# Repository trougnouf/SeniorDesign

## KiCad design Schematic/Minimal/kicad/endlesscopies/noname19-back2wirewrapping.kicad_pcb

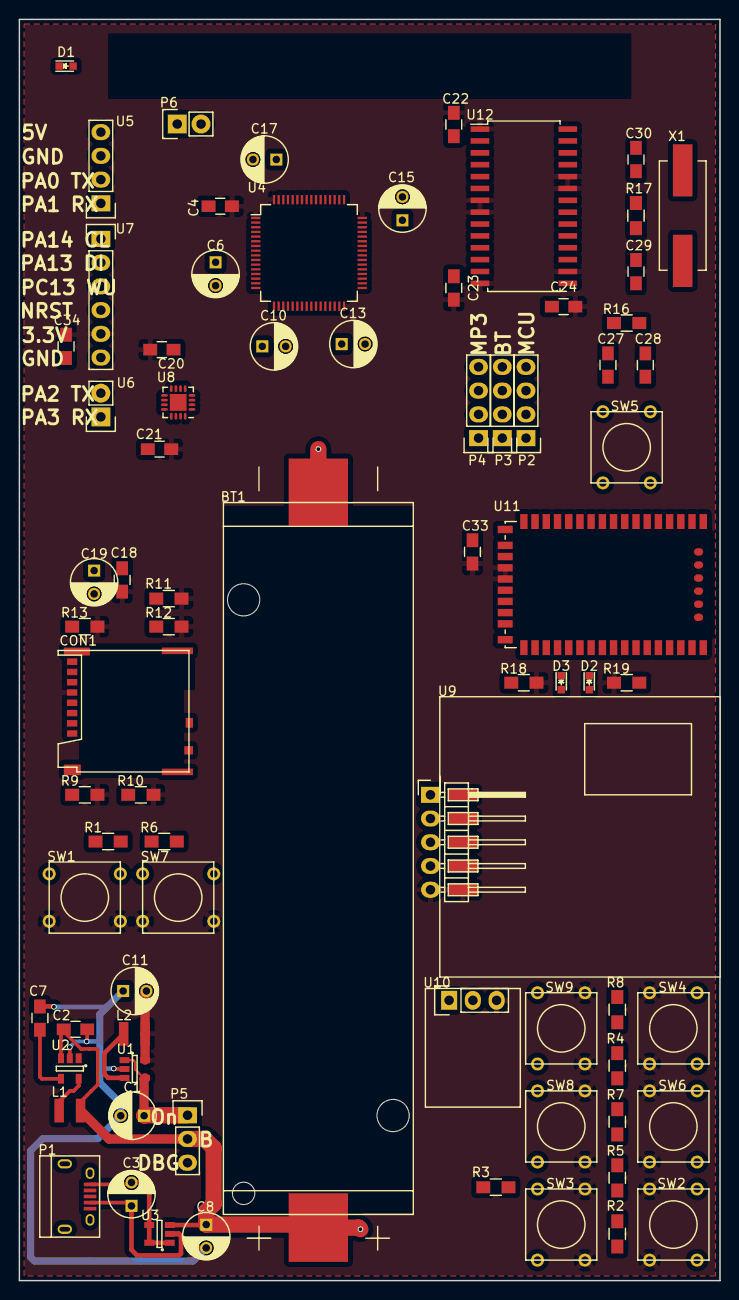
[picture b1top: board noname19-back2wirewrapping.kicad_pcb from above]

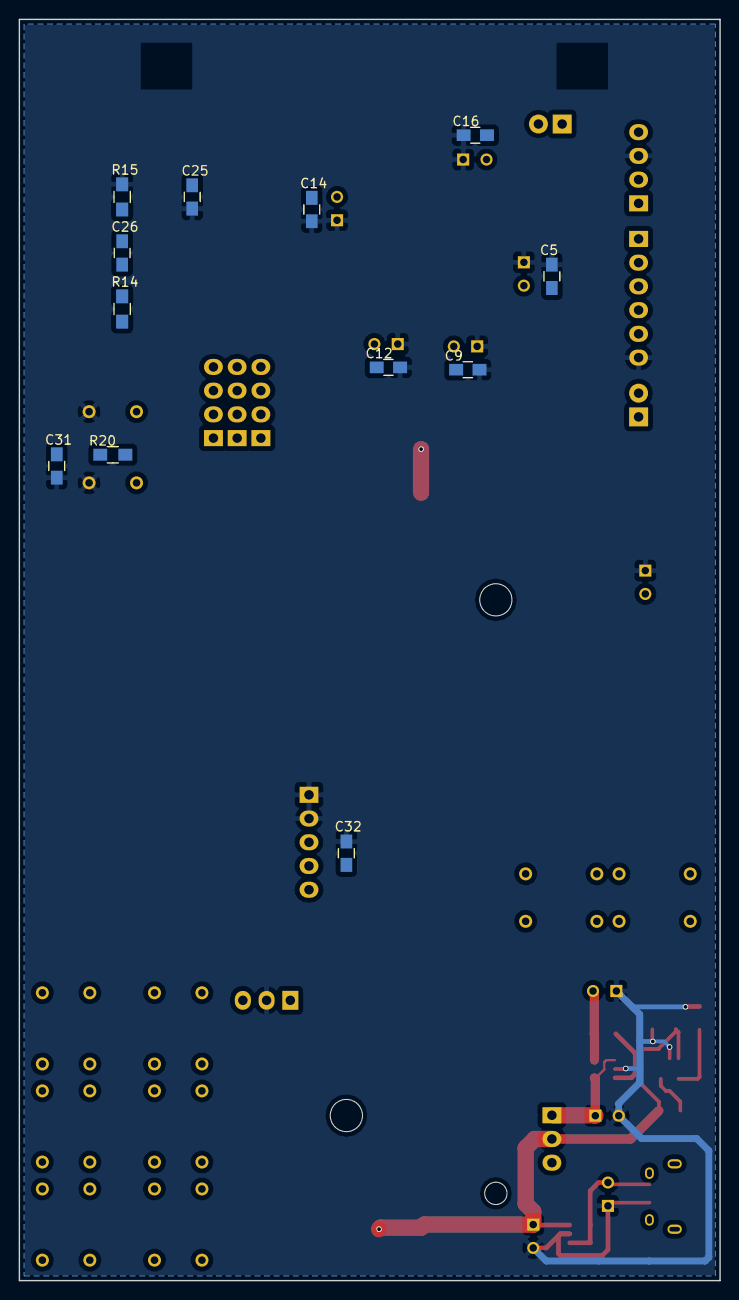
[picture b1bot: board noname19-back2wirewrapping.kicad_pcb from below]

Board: 2 copper layers, 75.0 x 135.0 mm, 89 parts (12 on the bottom side), 76 nets.

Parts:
BT1: Battery; 18650BatteryHolder
C1, C11: 10uF; C_Radial_D5_L11_P2.5
C2: 4.7uF; C_0805_HandSoldering
C3, C8: 1uF; C_Radial_D5_L11_P2.5
C4, C5, C9, C12, C14, C16, C19, C20, C21, C22, C23, C24, C25, C26, C31, C32, C33, C34: 0.1uF; C_0805_HandSoldering
C6, C10, C13, C15, C17: 4.7uF; C_Radial_D5_L11_P2.5
C7: 10uF; C_0805_HandSoldering
C18: 47uF; C_Radial_D5_L11_P2.5
C27: 470pF; C_0805_HandSoldering
C28: 4.7nF; C_0805_HandSoldering
C29, C30: 22pF; C_0805_HandSoldering
CON1: uSD_Card; MicroSD
D1: Led_Small; LED_0603
D2: Led_B; LED_0603
D3: Led_R; LED_0603
L1, L2: 4.7uH; Neosid_Inductor_SM-NE29_SMD1008
P1: USB_B; USB_Micro-B
P2, P3, P4: CONN_01X04; Pin_Header_Straight_1x04
P5: CONN_01X03; Pin_Header_Straight_1x03
P6: CONN_01X02; Socket_Strip_Straight_1x02
R1, R2, R3, R4, R5, R6, R7, R8, R20: 10K; R_0805_HandSoldering
R9, R10, R11, R12, R13: 47K; R_0805_HandSoldering
R14, R15: 4.7; R_0805_HandSoldering
R16: 1k; R_0805_HandSoldering
R17: 1M; R_0805_HandSoldering
R18: 470; R_0805_HandSoldering
R19: 47; R_0805_HandSoldering
SW1, SW2, SW3, SW4, SW5, SW6, SW7, SW8, SW9: SW_PUSH; SW_PUSH_SMALL
U1: PAM2301; SOT-23-5
U2: XC9140; SOT-23-5
U3: MCP73811/2; SOT-23-5
U4: STM32L476R; LQFP-64_10x10mm_Pitch0.5mm
U5: Lightware_SF10/A; Socket_Strip_Straight_1x04_3467
U6: UART; Socket_Strip_Straight_1x02
U7: DebugPins; Socket_Strip_Straight_1x06
U8: MLX90393; QFN-16-1EP_3x3mm_Pitch0.5mm
U9: LS20031; LS20031+H
U10: ADMP401-BB; INMP401-bb
U11: RN-52
U12: STA013; SOIC-28_7.5x17.9mm_Pitch1.27mm
X1: 14.7456MHz; Crystal_HC49-SD_SMD

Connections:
+3V3: C4.2, C5.2, C6.2, C9.2, C10.2, C11.2, C12.2, C13.2, C14.2, C15.2, C16.2, C17.2, C18.2, C19.1, C20.2, C21.2, C22.2, C23.2, C24.2, C25.2, C31.2, C32.1, C33.1, C34.1, CON1.4, L2.2, R9.2, R10.2, R11.2, R12.1, R13.1, R14.1, R18.1, R19.1, R20.1, SW1.2, SW2.2, SW3.2, SW4.2, SW6.2, SW7.2, SW8.2, SW9.2, U1.5, U4.1, U4.13, U4.19, U4.32, U4.48, U4.64, U7.5, U8.8, U8.15, U9.1, U10.3, U11.21, U11.22, U12.1, U12.7, U12.8, U12.14, U12.16, U12.23, U12.24
+5V: C7.1, U2.4, U5.7
+BATT: BT1.1, C2.1, C8.1, L1.1, P5.2, U2.3, U3.3
/3VEN: C1.1, P5.1, U1.1, U1.4
/5VEN: U2.1, U4.38
/in1: R5.2, SW6.1, U4.41
/in2: R6.2, SW7.1, U4.43
/in3: R7.2, SW8.1, U4.44
/in4: R8.2, SW9.1, U4.45
/in5: R1.2, SW1.1, U4.3
/in6: R2.2, SW2.1, U4.4
/in7: R3.2, SW3.1, U4.5
/in8: R4.2, SW4.1, U4.6
GND: BT1.2, C1.2, C2.2, C3.1, C4.1, C5.1, C6.1, C7.2, C8.2, C9.1, C10.1, C11.1, C12.1, C13.1, C14.1, C15.1, C16.1, C17.1, C18.1, C19.2, C20.1, C21.1, C22.1, C23.1, C24.1, C25.1, C27.2, C28.2, C29.2, C30.2, C31.1, C32.2, C33.2, C34.2, CON1.6, D1.1, P1.4, R1.1, R2.1, R3.1, R4.1, R5.1, R6.1, R7.1, R8.1, R15.1, SW5.2, U1.2, U2.2, U3.2, U4.12, U4.18, U4.31, U4.47, U4.63, U5.6, U7.6, U8.11, U8.12, U8.13, U9.4, U9.5, U10.2, U11.1, U11.18, U11.27, U11.39, U11.44, U11.45, U11.46, U11.47, U11.48, U11.49, U11.50, U12.2, U12.13, U12.15, U12.22, U12.25, U12.27
NRST: R20.2, SW5.1, U4.7, U7.4
unnamed: C3.2, P1.1, U3.1, U3.4, U3.5
unnamed: C26.1, R15.2, U12.18
unnamed: C26.2, R14.2, U12.17
unnamed: C27.1, R16.1, U12.19
unnamed: C28.1, R16.2
unnamed: C29.1, R17.2, U12.20, X1.1
unnamed: C30.1, R17.1, U12.21, X1.2
unnamed: D1.2, U4.61
unnamed: D2.1, U11.33
unnamed: D2.2, R19.2
unnamed: D3.1, U11.32
unnamed: D3.2, R18.2
unnamed: L1.2, U2.5
unnamed: L2.1, U1.3
unnamed: P3.1, U11.26
unnamed: P3.2, U11.25
unnamed: P3.3, U11.24
unnamed: P3.4, U11.23
unnamed: P4.1, U12.10
unnamed: P4.2, U12.11
unnamed: P4.4, U12.9
PA0_las: U4.14, U5.4
PA1_las: U4.15, U5.3
PA2_UART: U4.16, U6.2
PA3_UART: U4.17, U6.1
PA4_BTpcm-Sync: P2.2, U4.20
PA5_MP3-SCK: U4.21, U12.6
PA6_BT-RTS: U4.22, U11.14
PA7_MP3-SDI: U4.23, U12.5
PA9_GPS-RX: U4.42, U9.2
PA13_dbg: U4.46, U7.2
PA14_dbg: U4.49, U7.1
PA15_SD-DET: CON1.9, U4.50
PB0_mic: U4.26, U10.1
PB1_BT-CTS: U4.27, U11.15
PB2_BT-GP2: U4.28, U11.2
PB3_BTpcm-CLK: P2.1, U4.55
PB5_BTpcm-IN: P2.4, U4.57
PB7_GPS-TX: U4.59, U9.3
PB9_MAG-CS: U4.62, U8.2
PB10_MAG-SPC: U4.29, U8.3
PB11_BT-GP9: U4.30, U11.11
PB12_MAG-INT: U4.33, U8.1
PB13_MAG-TRIG: U4.34, U8.7
PB14_MP3-RST: U4.35, U12.26
PB15_MAG-MOSI: U4.36, U8.5
PC0_MP3-SCL: U4.8, U12.4
PC1_MP3-SDA: U4.9, U12.3
PC2_MAG-MISO: U4.10, U8.6
PC4_BT-RX: U4.24, U11.17
PC5_BT-TX: U4.25, U11.16
PC6_MP3-DR: U4.37, U12.28
PC8_SD-D0: CON1.7, R10.1, U4.39
PC9_SD-D1: CON1.8, R9.1, U4.40
PC10_SD-D2: CON1.1, R13.2, U4.51
PC11_SD-D3: CON1.2, R12.2, U4.52
PC12_SD-CK: CON1.5, U4.53
PC13_dbg: U4.2, U7.3
PD2_SD-CMD: CON1.3, R11.1, U4.54
x-in-1: P6.2, U4.56
x-in-2: P6.1, U4.58
